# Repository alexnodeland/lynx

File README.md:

<p align="center">

  <br>

</p>

# lynx

**An open-source pan/tilt camera you can tell where to look.** AI agents drive it over MCP, Home Assistant finds it on its own, and it tracks faces and learns your own objects without sending a frame off the device.

It runs on a Seeed XIAO ESP32-S3 Sense with two MG90S servos and eight 3D-printed parts. One USB-C cable powers it, and one screw type holds it together. **About $43 in parts** ([cost breakdown](hardware/production/BOM.md#cost)).

**Site:** https://alexnodeland.github.io/lynx/ · **[Web flasher](https://alexnodeland.github.io/lynx/flash.html)** · **[Build guide (3D)](https://alexnodeland.github.io/lynx/build.html)** · **[Docs](docs/README.md)**

## What it does

### Agents: an MCP server on the camera

The firmware is an MCP server (Streamable HTTP) and a REST API. Give an agent the URL and the device token, and it can aim the head, take a snapshot with the detections drawn on it, find faces, save presets, run a patrol, and read the microSD recordings.

```sh
claude mcp add --transport http lynx http://lynx-xxxx.local/mcp --header "Authorization: Bearer <token>"
```

> **you:** look at the desk and take a picture
> → `look(pan: -40, tilt: 30)` → `snapshot(annotate: true)`
> **agent:** A laptop, a mug and a plant. One person, seated on the left.

Tools: `look` · `center` · `sweep` · `snapshot` · `detect` · `follow` · `preset` · `patrol` · `recordings` · `set_camera` · `stream_url` · `status`. Full list and the REST API: [`firmware/lynx`](firmware/lynx#mcp).

### Home Assistant: discovered, not configured

Add this repo to HACS as a custom integration and lynx shows up under *Discovered* (zeroconf). Paste the token and you get the camera with live view, pan and tilt sliders, occupancy and a person count, follow and detection switches, presets and patrol, microSD recording, and a firmware update entity that installs GitHub releases over Wi-Fi.

```yaml
# look at the front door when it opens
triggers:
  - trigger: state
    entity_id: binary_sensor.front_door
    to: "on"
actions:
  - action: lynx.look
    target: { entity_id: camera.lynx_42e0 }
    data: { pan: 60, tilt: 50 }
```

Entities and more automations: [`custom_components/lynx`](custom_components/lynx).

### Face tracking, on the device

ESP-DL finds human faces or cat faces at about 4 fps on a scaled copy of each frame, so the stream keeps its 20 fps. **Follow mode** keeps the nearest face centred with small no-overshoot moves, holds where it last saw one, then glides back to rest. It's detection, not recognition, and nothing leaves the camera unless you ask for it over the API.

### Your own detector

Anything else (a package, your dog, a whole person) comes from Edge Impulse. lynx collects its own training set by scanning the room, and one command installs the export:

```sh
just capture mug              # lynx pans the room and saves 30 shots to datasets/mug/
# label and train in Edge Impulse (FOMO boxes or a classifier), export as an Arduino library
just model-add export.zip     # now `model: custom` in the API, MCP and Home Assistant
```

Walkthrough: [docs/custom-models.md](docs/custom-models.md).

### Also

Over-the-air updates that roll themselves back if a new build fails · up to 4 viewers at once and pushed status events · 8 named presets and a patrol tour · snapshots on detection and a timelapse on microSD · a first-boot Wi-Fi hotspot with a setup page · a per-device token.

## Repository

| Path | Contents |
|------|----------|
| [`firmware/lynx`](firmware/lynx) | PlatformIO firmware: motion, camera and MJPEG stream, REST API, MCP server, detection and follow, OTA, setup hotspot |
| [`custom_components/lynx`](custom_components/lynx) | Home Assistant integration (HACS) |
| [`hardware/production`](hardware/production) | Print-ready STL/STEP, assembly STEP, [BOM](hardware/production/BOM.md) |
| [`hardware/electronics`](hardware/electronics) | Circuit, nets, parts, wiring harness, carrier PCB (KiCad) |
| [`web`](web) | three.js landing page, build guide and web flasher (Vite + GSAP) |
| [`tools/ml`](tools/ml) | Training-image capture for custom models |
| `media` | Renders and screenshots |

## Specs

| | |
|---|---|
| Controller | Seeed XIAO ESP32-S3 Sense (camera, microSD, Wi-Fi) |
| Actuators | 2 × MG90S micro servo — pan on D0 (GPIO1), tilt on D1 (GPIO2), 220 Ω series resistors |
| Travel | pan ±90°, tilt ±60° mechanical; firmware soft limits pan ±88°, tilt ±58° |
| Motion | eased "glance" moves, default max speed 300 °/s, PWM detached when idle |
| Power + data | one USB-C cable via a panel socket in the base (Adafruit 6069); supply ≥ 1 A |
| Decoupling | 470 µF 6.3 V bulk + 100 nF across the servo 5 V rail |
| Fasteners | 9 × M2 × 8 thread-forming, pan head — the only screw |
| Printed parts | 8 (base, lid, battery tray, yoke, pan base, pan cap, servo shroud, light pipe) |
| Control | on your network: REST API, MCP server for AI agents, MJPEG stream (port 81), dashboard; per-device token; serial console |
| Setup | first-boot Wi-Fi hotspot `lynx-xxxx` with a captive setup page; `lynx-xxxx.local` via mDNS |
| Detection | on-device faces or cat faces (ESP-DL), ~4 fps; custom Edge Impulse models; follow mode |
| Rest pose | pan 0°, tilt 45°: the lens leans toward the front (tilt 0° points it straight up) |
| Battery | optional 150 mAh LiPo keeps the camera up; servos run on USB power only |

## System

```mermaid
flowchart LR
  USB["USB-C supply (≥ 1 A)"] --> SOCK["Panel socket<br/>Adafruit 6069"]
  SOCK --> XIAO["XIAO ESP32-S3 Sense"]
  BAT["LiPo 150 mAh<br/>(optional)"] -.-> XIAO
  XIAO -- "5V / GND" --> RAIL["Servo rail<br/>470 µF + 100 nF"]
  XIAO -- "D0 → 220 Ω" --> PAN["Pan servo<br/>MG90S"]
  XIAO -- "D1 → 220 Ω" --> TILT["Tilt servo<br/>MG90S"]
  RAIL --> PAN
  RAIL --> TILT
  XIAO -. "Wi-Fi: MCP" .- AGENT["AI agent"]
  XIAO -. "Wi-Fi: REST + events" .- HA["Home Assistant"]
  XIAO -. "Wi-Fi: dashboard + MJPEG" .- CLIENT["Browser"]
```

## Gallery

| | |
|---|---|
|  |  |
| Exploded: eight parts, one screw type | Assembled on the pan base |
|  |  |
| One USB-C cable into the base | microSD slot above the USB-C port |
|  |  |
| The landing page | Its motion section |

## Parts

About **$43** per camera, **$55** with the battery and a microSD card, and about $80 for your first build because the small parts come in packs ([breakdown](hardware/production/BOM.md#cost)). Full list with suppliers in [`hardware/production/BOM.md`](hardware/production/BOM.md).

| Qty | Part |
|---|---|
| 8 | printed parts (`hardware/production/*.stl`) |
| 1 | Seeed XIAO ESP32-S3 Sense |
| 2 | MG90S micro servo (Waveshare 15024) or Adafruit SG92R |
| 1 | panel-mount USB-C extension, Adafruit 6069 |
| 1 | right-angle USB-C to USB-C, thin, data-capable, 15–20 cm |
| 1 | 470 µF 6.3 V electrolytic (Panasonic EEU-FR0J471) + 100 nF 0603 |
| 2 | 220 Ω resistor |
| 9 | M2 × 8 thread-forming screw, pan head |
| 1 | 12.7 × 3.17 mm N42 disc magnet (K&J D82) |
| — | optional: 150 mAh LiPo (Adafruit 1317), microSD card |

## Quick start

### 1. Print

Print the three `test-*.stl` fit coupons first, then the eight parts in [`hardware/production`](hardware/production). Orientation, supports and materials per part are in the [BOM](hardware/production/BOM.md#printed-parts); defaults are 0.2 mm layers and 3 walls.

### 2. Assemble

The **[interactive build guide](https://alexnodeland.github.io/lynx/build.html)** walks all 13 steps in 3D:
parts fly in, the rest of the camera stays ghosted, and you can orbit the model at every step. The same steps as text:

Follow the ten steps in the [BOM's assembly section](hardware/production/BOM.md#assembly). Wire the servos as in [`hardware/electronics`](hardware/electronics) — carrier PCB or soldered harness, same nets.

### 3. Flash

The easiest way is from a browser: open the [web flasher](https://alexnodeland.github.io/lynx/flash.html) in Chrome or Edge, plug in over USB-C, and click Install. Or with PlatformIO:

```sh
cd firmware/lynx
pio run -e xiao -t upload       # build and flash over USB-C
pio device monitor -b 115200    # serial console: try `info`, `center`, `sweep`
```

Calibrate before fixing the horns: see [`firmware/lynx`](firmware/lynx#calibration).

### 4. Connect

On first boot lynx opens a Wi-Fi hotspot, **`lynx-xxxx`**. Join it from a phone, pick your network, and save the token the setup page shows. Then open `http://lynx-xxxx.local/` for the live view and controls, or hook up an AI agent:

```sh
claude mcp add --transport http lynx http://lynx-xxxx.local/mcp --header "Authorization: Bearer <token>"
```

The full API and MCP tool list are in [`firmware/lynx`](firmware/lynx#http-api).

**Home Assistant:** add this repo to HACS as a custom integration, restart, and lynx shows up under *Discovered*. Paste the token and you're done. See [`custom_components/lynx`](custom_components/lynx).

### 5. Run the site locally

```sh
cd web
npm ci
npm run dev
```

## Develop

```sh
just setup   # once: PlatformIO + HA test harness in .venv, web deps, git hooks
just check   # lint, 71 firmware tests, XIAO build, 35 Home Assistant tests, site build
just         # every other recipe: fw-flash, fw-monitor, web-dev, hass-test, look, snap, mcp-add, release …
```

[Contributing](CONTRIBUTING.md) · [Architecture](docs/architecture.md) · [Troubleshooting](docs/troubleshooting.md) · [Changelog](CHANGELOG.md)

## Licences

- Hardware: CERN-OHL-S-2.0
- Firmware and web: MIT
- Docs and media: CC-BY-SA-4.0

The licence texts are in [`LICENSES/`](LICENSES). The root [`LICENSE`](LICENSE) is the MIT text for the software, so GitHub and HACS can detect it; [`NOTICE`](NOTICE) maps each folder to its licence.

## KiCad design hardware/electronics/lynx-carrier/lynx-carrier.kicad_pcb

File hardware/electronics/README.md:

<!-- SPDX-License-Identifier: CERN-OHL-S-2.0 -->
# lynx electronics

lynx has very little electronics of its own: the Seeed XIAO ESP32-S3 Sense does the work, and
two hobby servos move it. What needs designing is how power and the two servo signals get from
the XIAO to the servos. You can build it two ways — both use the same nets.

| Option | What it is | When to choose it |
|---|---|---|
| **A. Carrier PCB** (`lynx-carrier/`) | An 18 × 14 mm, 2-layer board that sits in the power pod: two 3-pin servo headers, the bulk capacitor, series resistors, and a 4-pin lead to the XIAO. | Cleanest build; servos unplug; recommended. |
| **B. Wiring harness** (`harness/`) | The same circuit as soldered splices with heat-shrink, no PCB. | No PCB order; fine for a one-off. |

## Circuit

```mermaid
flowchart LR
  subgraph XIAO["XIAO ESP32-S3 Sense"]
    V5["5V"]
    G["GND"]
    D0["D0 / GPIO1"]
    D1["D1 / GPIO2"]
  end
  subgraph CAR["Carrier PCB or harness"]
    C1["C1 470 µF"]
    C2["C2 100 nF"]
    R1["R1 220 Ω"]
    R2["R2 220 Ω"]
  end
  V5 --> C1
  V5 --> C2
  G --> C1
  G --> C2
  D0 --> R1 --> J2["J2 pan servo"]
  D1 --> R2 --> J3["J3 tilt servo"]
  V5 --> J2
  V5 --> J3
```

```text
            XIAO ESP32-S3 Sense                       carrier PCB (in the power pod)
          ┌──────────────────────┐   4-wire lead    ┌──────────────────────────────────┐
  USB-C ──┤ USB-C          5V ●──┼──── red ─────────┤ +5V ──┬──────┬──────────┬────────── │
 (from    │                GND ●─┼──── black ───────┤ GND ──┼──┬───┼──┬───────┼──┬────── │
  base    │                 D0 ●─┼──── orange ──────┤ PAN ─[220R]─┐ │  │       │  │      │
  socket) │                 D1 ●─┼──── yellow ──────┤ TILT ─[220R]┼─┼──┼─┐     │  │      │
          └──────────────────────┘                  │       C1 470µ │ C2 100n │  │      │
                                                    │  J2 PAN  [S + −]   J3 TILT [S + −] │
                                                    └──────────────────────────────────┘
```

| Net | XIAO pad | Carrier | Servo pin | Notes |
|---|---|---|---|---|
| `+5V` | 5V (USB VBUS) | J1-1, J2-2, J3-2, C1+, C2 | red | live only on USB power: on battery the servos stop, the camera keeps running |
| `GND` | GND | J1-2, J2-3, J3-3, C1−, C2 | brown / black | |
| `PAN` | D0 (GPIO1) | J1-3 → R1 220 Ω → J2-1 | orange | series R limits ringing and protects the GPIO |
| `TILT` | D1 (GPIO2) | J1-4 → R2 220 Ω → J3-1 | orange | |

**Why these parts.** An MG90S draws up to ~0.7–1 A at stall. C1 (470 µF, 6.3 V, low-ESR) carries
the inrush when a servo starts so the 5 V rail — and the ESP32 — don't brown out; C2 (100 nF)
takes the high-frequency noise from the servo motors. 3.3 V logic drives SG90/MG90S signal
inputs reliably, so no level shifter is needed. Use a USB supply rated **≥ 1 A**.

## Parts (electronics)

| Ref | Part | Footprint | Orderable as |
|---|---|---|---|
| U1 | Seeed XIAO ESP32-S3 Sense | — (module) | Seeed 113991115 |
| J1 | 4-pin JST-SH 1.0 mm, side entry | JST_SH_SM04B-SRSS-TB_1x04-1MP_P1.00mm_Horizontal | JST SM04B-SRSS-TB (LCSC C160390) + 1.0 mm pre-crimped lead |
| J2, J3 | 3-pin 2.54 mm male header | PinHeader_1x03_P2.54mm_Vertical | any 2.54 mm header strip |
| C1 | 470 µF 6.3 V aluminium, Ø6.3 × 11.2 | CP_Radial_D6.3mm_P2.50mm | Panasonic EEU-FR0J471 |
| C2 | 100 nF 16 V X7R 0603 | C_0603_1608Metric | Samsung CL10B104KO8NNNC (LCSC C14663) |
| R1, R2 | 220 Ω 1 % 0603 | R_0603_1608Metric | Yageo RC0603FR-07220RL (LCSC C22962) |
| M1, M2 | MG90S micro servo | — | Waveshare 15024 |

## Carrier PCB (option A)

| Top | Bottom |
|---|---|
|  |  |

The whole KiCad 10 project is generated by [`lynx-carrier/make_carrier.py`](lynx-carrier/make_carrier.py):
`just pcb` writes the schematic and board, autoroutes it with Freerouting, fills the ground pours,
runs ERC and DRC (with schematic parity) and fails unless both are clean, then exports to
`lynx-carrier/fab/`:

| File | For |
|---|---|
| `lynx-carrier-gerbers.zip` | Gerbers + Excellon drill, upload to any fab (JLCPCB rules: 0.15 mm track/space, 0.3 mm drill) |
| `lynx-carrier-bom.csv`, `lynx-carrier-cpl.csv` | JLCPCB assembly: BOM with LCSC numbers, pick-and-place |
| `lynx-carrier-schematic.pdf`, `lynx-carrier-board.pdf/` (one PDF per layer) | Review |
| `lynx-carrier.step` | Fit check in the power pod |
| `erc.rpt`, `drc.rpt` | The checks the generator ran |

2 layers, 1.6 mm, 18 × 14 mm, ground poured on both sides. C1 and the two headers are
through-hole: hand-solder them after assembly, or order them as through-hole assembly.
Not yet fabricated or tested on a real board.

## Harness (option B)

See [`harness/lynx-harness.svg`](harness/lynx-harness.svg) (generated by `harness/make_harness.py`): cut the servo leads to length, splice signal / +5 V / GND per
the table above, put C1 across +5 V/GND at the splice, slide 3 mm heat-shrink over every joint.
Wire lengths are taken from the CAD cable route (enclosure → yoke clips → pod: ~120 mm).

## Open item: data through the base socket

Flashing an assembled lynx (from the web flasher or `pio run -t upload`) goes through
the base's USB-C panel socket (Adafruit 6069) and the internal right-angle cable. That
needs the socket to pass the USB 2.0 data pair (D+/D−), not just power. Confirm it on
the first build. If it carries power only, flash the XIAO before it goes into the pod,
or through its own port with the lid off. Once lynx is on Wi-Fi it doesn't need the
data pair: control, snapshots and video all go over the network.

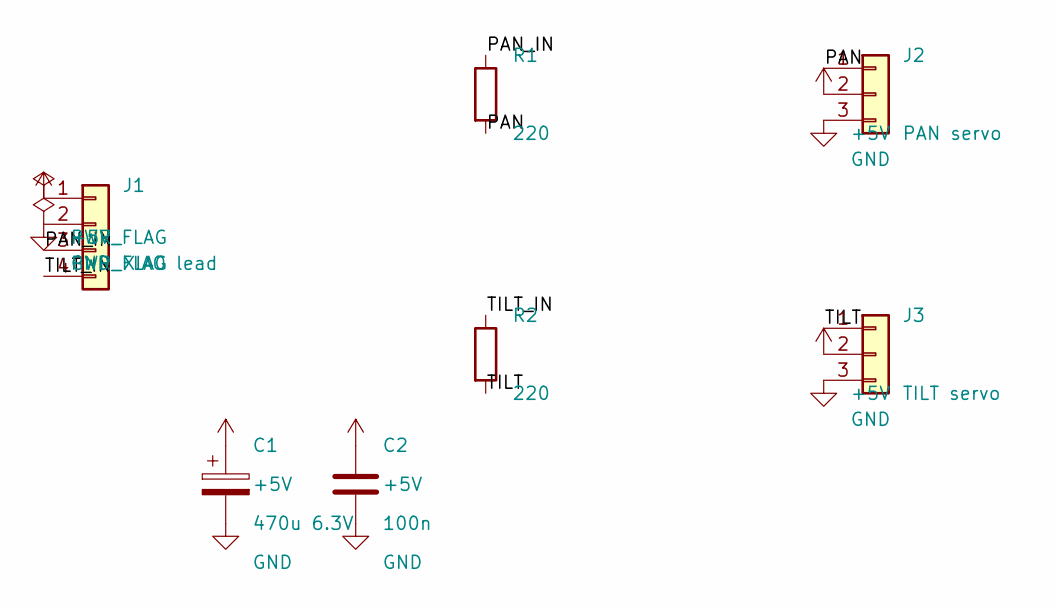
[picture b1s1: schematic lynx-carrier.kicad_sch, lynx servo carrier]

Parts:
C1: 470u 6.3V; CP_Radial_D6.3mm_P2.50mm; MPN Panasonic EEU-FR0J471
C2: 100n; C_0603_1608Metric; MPN Samsung CL10B104KO8NNNC; LCSC C14663
J1: XIAO lead; JST_SH_SM04B-SRSS-TB_1x04-1MP_P1.00mm_Horizontal; MPN JST SM04B-SRSS-TB; LCSC C160390
J2: PAN servo; PinHeader_1x03_P2.54mm_Vertical; MPN 2.54 mm 1x3 header
J3: TILT servo; PinHeader_1x03_P2.54mm_Vertical; MPN 2.54 mm 1x3 header
R1, R2: 220; R_0603_1608Metric; MPN Yageo RC0603FR-07220RL; LCSC C22962

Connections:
+5V: C1.1, C2.1, J1.1, J2.2, J3.2
/PAN: J2.1, R1.2
/PAN_IN: J1.3, R1.1
/TILT: J3.1, R2.2
/TILT_IN: J1.4, R2.1
GND: C1.2, C2.2, J1.2, J2.3, J3.3

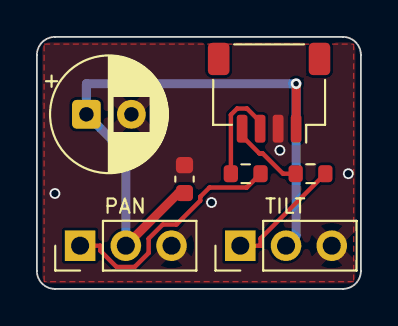
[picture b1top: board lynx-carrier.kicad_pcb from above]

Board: 2 copper layers, 18.0 x 14.0 mm, 7 parts (0 on the bottom side), 6 nets.

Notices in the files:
README.md:
Hardware licence
hardware/electronics/README.md:
Licence: CERN-OHL-S-2.0
